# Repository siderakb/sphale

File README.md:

# Sphale

Pro Micro/Proton C compatible [STM32F303CC](https://www.st.com/en/microcontrollers-microprocessors/stm32f303cc.html) board, specialized design for [QMK](https://github.com/qmk/qmk_firmware) keyboards.

> ***Sphale***rite  

## Board Characteristics

-  Copper layer count: 2
-  Board thickness: 1.6 mm
-  Board overall dimensions: 17.78 x 33.02 mm (0.7 x 1.3 inch)
-  Min track/spacing: 0.13 mm / 0.13 mm
-  Min hole diameter: 0.3 mm
-  Castellated pads: No
-  Edge card connectors: No
-  Plated board edge: No

## Disclaimer

These files are provided without warranty of any kind.  
Including but not limited to manufacturing, assembly, procurement and use at your own risk.  
It is recommended to check yourself before use.

For the full statement, please see [LICENSE](./LICENSE).

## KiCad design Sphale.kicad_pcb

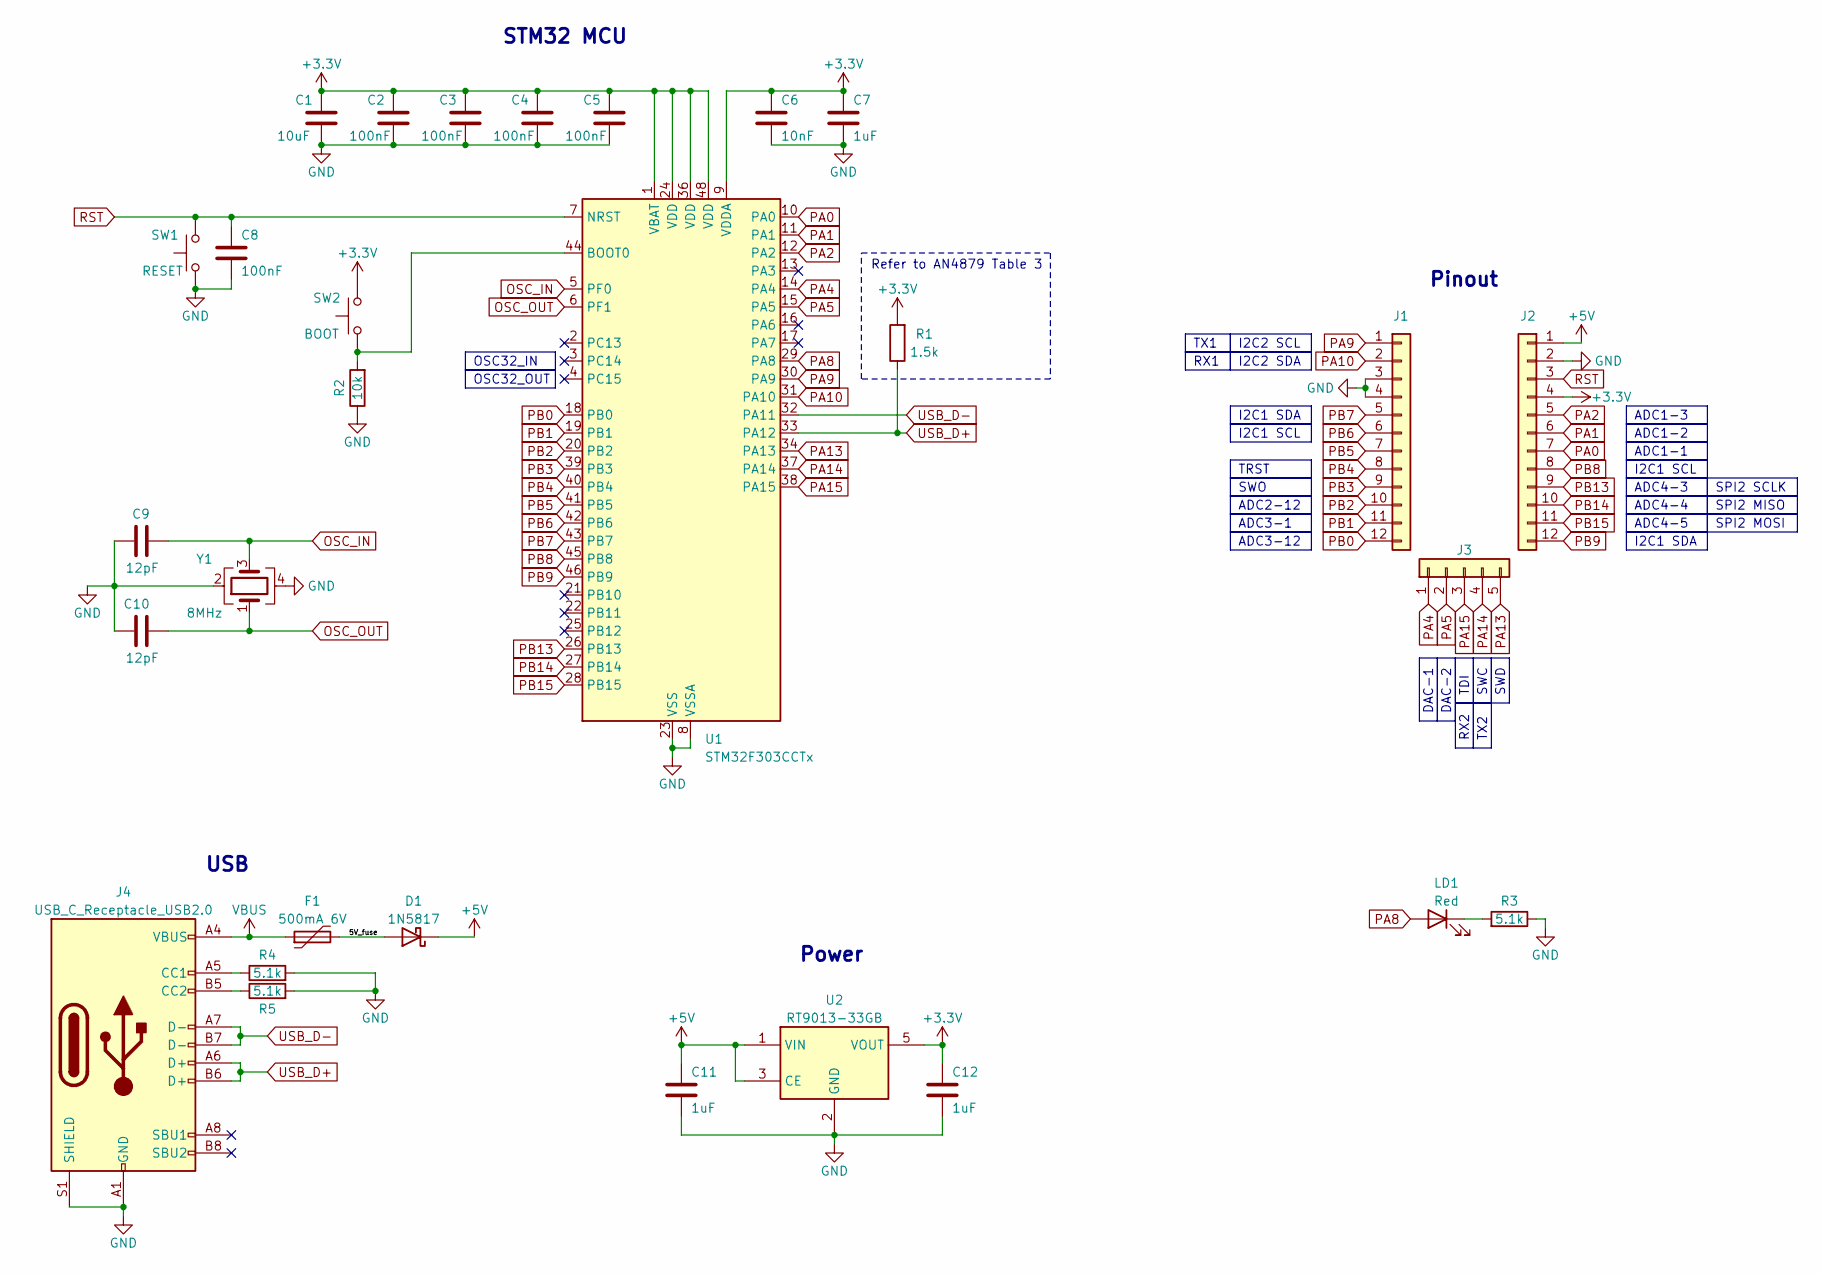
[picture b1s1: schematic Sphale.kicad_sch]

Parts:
C1: 10uF; C_0402_1005Metric; MFR. Part# CL05A106MQ5NUNC; LCSC C15525
C2, C3, C4, C5, C8: 100nF; C_0402_1005Metric; MFR. Part# CL05B104KO5NNNC; LCSC C1525
C6: 10nF; C_0402_1005Metric; MFR. Part# CL05B103KB5NNNC; LCSC C15195
C7, C11, C12: 1uF; C_0402_1005Metric; MFR. Part# CL05A105KA5NQNC; LCSC C52923
C9, C10: 12pF; C_0402_1005Metric; MFR. Part# 0402CG120J500NT; LCSC C1547
D1: 1N5817; D_SOD-323_HandSoldering; MFR. Part# B5817WS; LCSC C123899
F1: 500mA 6V; Fuse_0805_2012Metric; MFR. Part# SMD0805B050TF; LCSC C269104
J1, J2: Conn_01x12; PinHeader_1x12_P2.54mm_Vertical
J3: Conn_01x05; PinHeader_1x05_P2.54mm_Vertical
J4: USB_C_Receptacle_USB2.0; USB_C_Receptacle_HRO_TYPE-C-31-M-12; MFR. Part# TYPE-C-31-M-12; LCSC C165948
LD1: Red; LED_0603_1608Metric; MFR. Part# KT-0603R; LCSC C2286
R1: 1.5k; R_0402_1005Metric; MFR. Part# ARG02BTC1501; LCSC C2984410
R2: 10k; R_0402_1005Metric; MFR. Part# 0402WGF1002TCE; LCSC C25744
R3, R4, R5: 5.1k; R_0402_1005Metric; MFR. Part# 0402WGF5101TCE; LCSC C25905
SW1: RESET; SW_SPST_B3U-1000P; MFR. Part# TS-1064S-A1B2-D4; LCSC C498294
SW2: BOOT; SW_SPST_B3U-1000P; MFR. Part# TS-1064S-A1B2-D4; LCSC C498294
U1: STM32F303CCTx; LQFP-48_7x7mm_P0.5mm; MFR. Part# STM32F303CCT6; LCSC C81523
U2: RT9013-33GB; SOT-23-5; MFR. Part# TPRT9013-33GB; LCSC C587158
Y1: 8MHz; Crystal_SMD_3225-4Pin_3.2x2.5mm; MFR. Part# X32258MSB4SI; LCSC C2682774

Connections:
+3.3V: C1.1, C2.1, C3.1, C4.1, C5.1, C6.1, C7.1, C12.1, J2.4, R1.2, SW2.2, U1.1 (VBAT), U1.9 (VDDA), U1.24 (VDD), U1.36 (VDD), U1.48 (VDD), U2.5 (VOUT)
+5V: C11.1, D1.1 (K), J2.1, U2.1 (VIN), U2.3 (CE)
/5V_fuse: D1.2 (A), F1.2
GND: C1.2, C2.2, C3.2, C4.2, C5.2, C6.2, C7.2, C8.2, C9.1, C10.1, C11.2, C12.2, J1.3, J1.4, J2.2, J4.A1 (GND), J4.A12 (GND), J4.B1 (GND), J4.B12 (GND), J4.S1 (SHIELD), R2.1, R3.1, R4.2, R5.2, SW1.1, U1.8 (VSSA), U1.23 (VSS), U1.35 (VSS), U1.47 (VSS), U2.2 (GND), Y1.2, Y1.4
unnamed: J4.A5 (CC1), R4.1
unnamed: J4.B5 (CC2), R5.1
unnamed: LD1.1 (K), R3.2
unnamed: R2.2, SW2.1, U1.44 (BOOT0)
OSC_IN: C9.2, U1.5 (PF0), Y1.3
OSC_OUT: C10.2, U1.6 (PF1), Y1.1
PA0: J2.7, U1.10 (PA0)
PA1: J2.6, U1.11 (PA1)
PA2: J2.5, U1.12 (PA2)
PA4: J3.1, U1.14 (PA4)
PA5: J3.2, U1.15 (PA5)
PA8: LD1.2 (A), U1.29 (PA8)
PA9: J1.1, U1.30 (PA9)
PA10: J1.2, U1.31 (PA10)
PA13: J3.5, U1.34 (PA13)
PA14: J3.4, U1.37 (PA14)
PA15: J3.3, U1.38 (PA15)
PB0: J1.12, U1.18 (PB0)
PB1: J1.11, U1.19 (PB1)
PB2: J1.10, U1.20 (PB2)
PB3: J1.9, U1.39 (PB3)
PB4: J1.8, U1.40 (PB4)
PB5: J1.7, U1.41 (PB5)
PB6: J1.6, U1.42 (PB6)
PB7: J1.5, U1.43 (PB7)
PB8: J2.8, U1.45 (PB8)
PB9: J2.12, U1.46 (PB9)
PB13: J2.9, U1.26 (PB13)
PB14: J2.10, U1.27 (PB14)
PB15: J2.11, U1.28 (PB15)
RST: C8.1, J2.3, SW1.2, U1.7 (NRST)
USB_D+: J4.A6 (D+), J4.B6 (D+), R1.1, U1.33 (PA12)
USB_D-: J4.A7 (D-), J4.B7 (D-), U1.32 (PA11)
VBUS: F1.1, J4.A4 (VBUS), J4.A9 (VBUS), J4.B4 (VBUS), J4.B9 (VBUS)

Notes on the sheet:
SWD
I2C1 SCL
ADC4-5
TX2
DAC-1
OSC32_IN
I2C1 SDA
ADC4-4
ADC4-3
SPI2 SCLK
SPI2 MISO
ADC3-1
DAC-2
OSC32_OUT
I2C2 SCL
RX2
TDI
SWC
SWO
ADC1-3
TX1
TRST
ADC1-2
SPI2 MOSI
ADC1-1
I2C2 SDA
ADC3-12
ADC2-12
RX1
USB
Power
Refer to AN4879 Table 3
STM32 MCU
Pinout

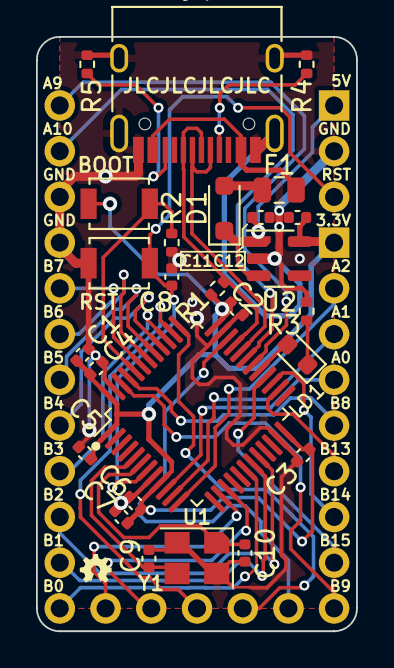
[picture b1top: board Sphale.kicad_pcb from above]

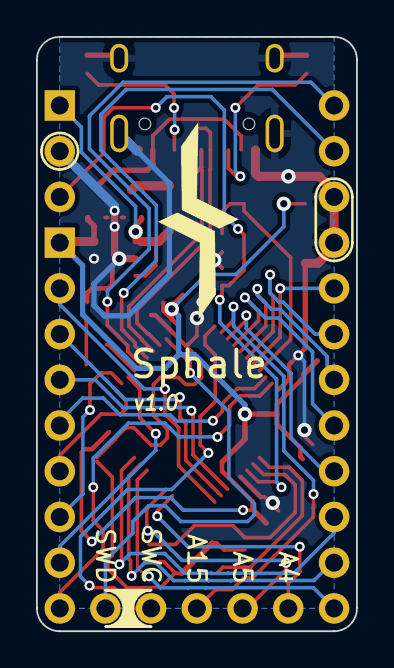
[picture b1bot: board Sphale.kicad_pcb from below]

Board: 2 copper layers, 17.8 x 33.0 mm, 29 parts (2 on the bottom side), 38 nets.

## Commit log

2023-06-19 Init commit
2023-06-19 Create LICENSE
2023-06-19 Add .gitignore
2023-06-25 Update URL, replace "ziteh" with "siderakb".
2023-07-08 Update BOM and references
